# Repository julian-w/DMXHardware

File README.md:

# DMXHardware
DMX Hardware (and Firmware) which allows you build your own DMX equipment

work in progress...

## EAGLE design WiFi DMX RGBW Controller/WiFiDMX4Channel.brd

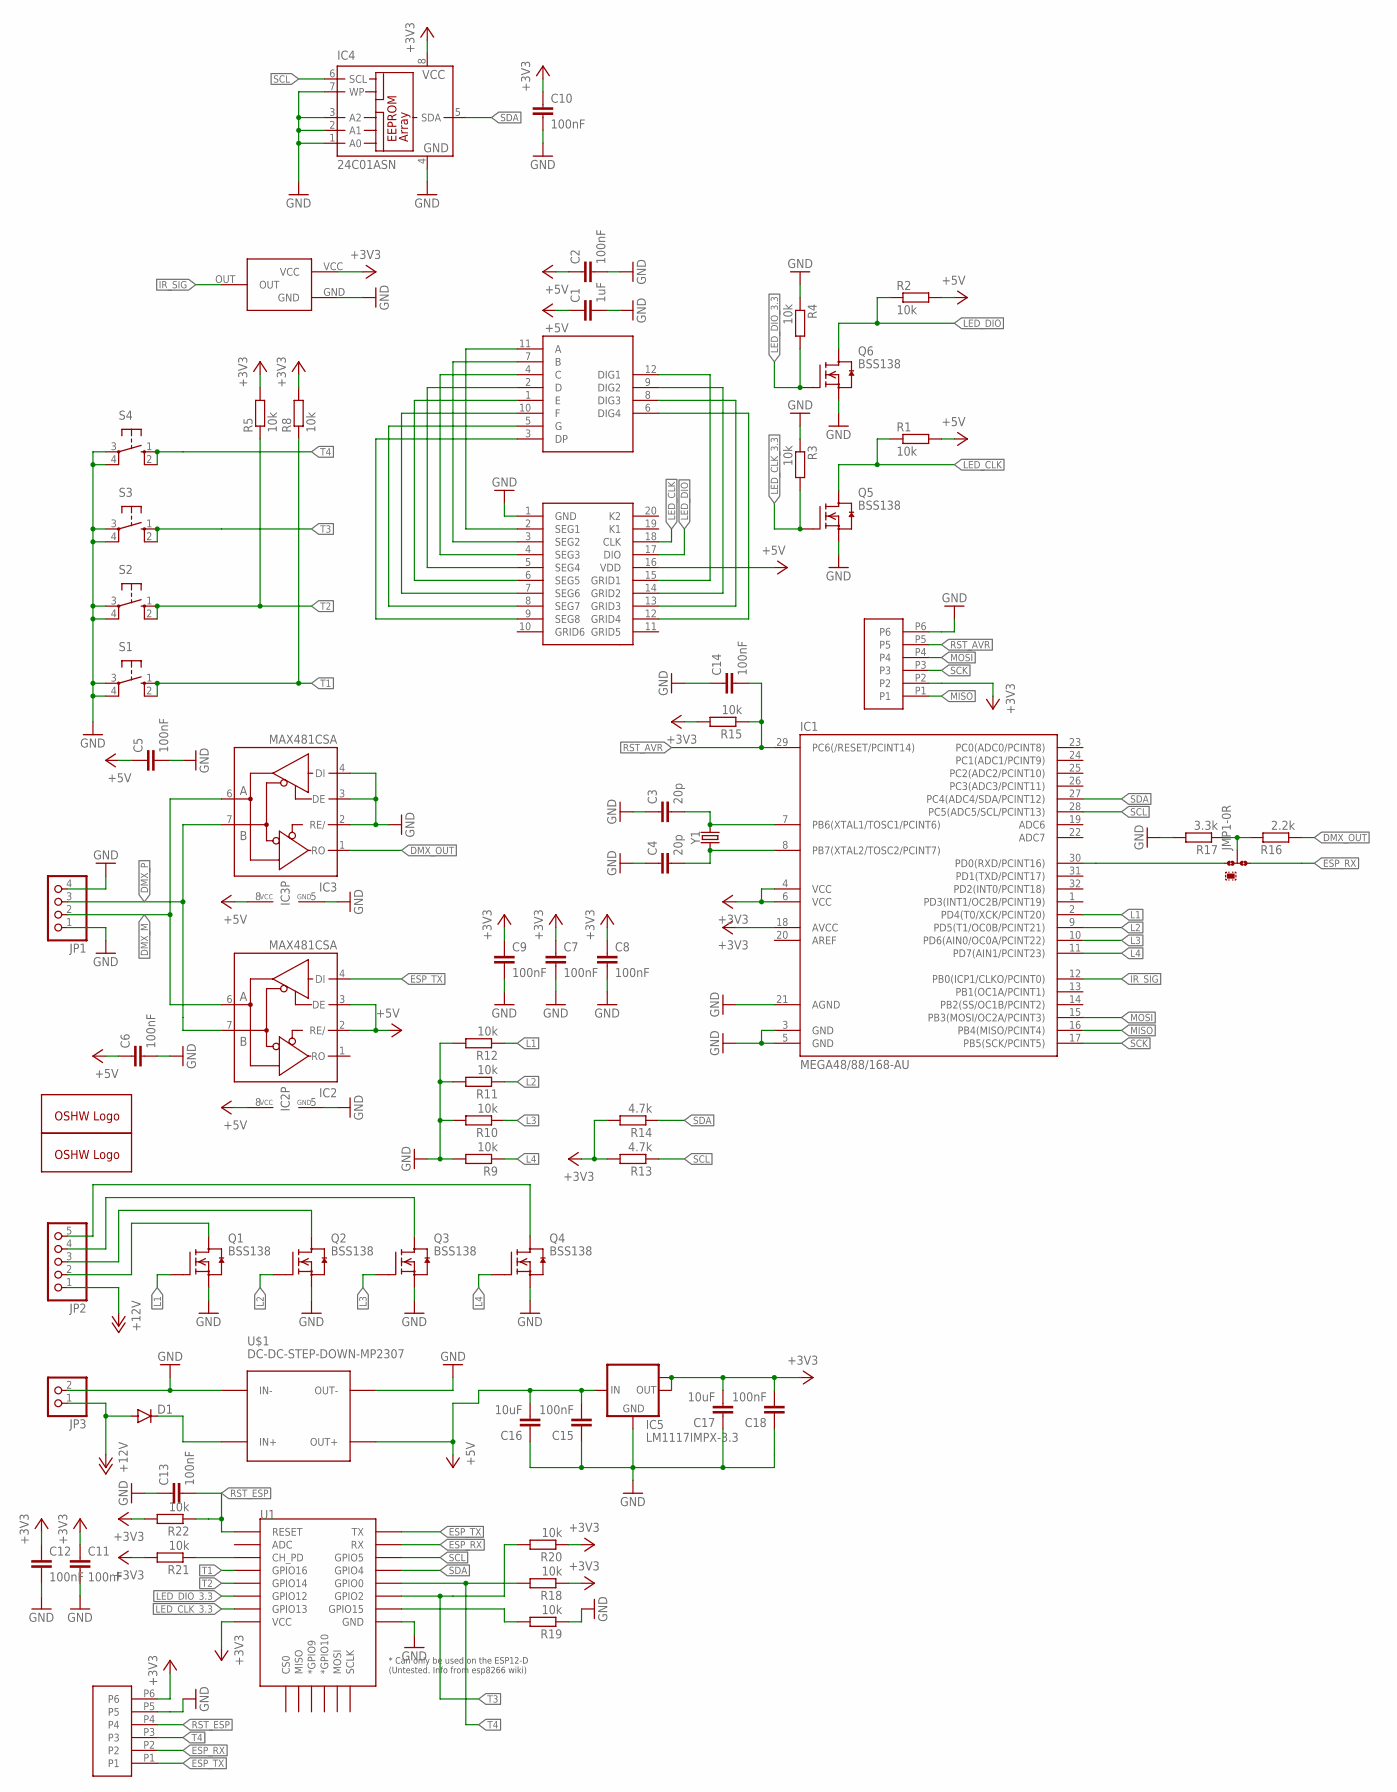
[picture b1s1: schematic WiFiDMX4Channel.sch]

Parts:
C1: 1uF; C0603
C2, C5, C6, C7, C8, C9, C10, C11, C12, C13, C14, C15, C18: 100nF; C0603
C3, C4: 20p; C0603
C16, C17: 10uF; C0603
D1: DIODE-DO214AC; DO214AC
GOLD_ORB_SM1, GOLD_ORB_SM2: OSHWLOGOLOGO5MM; OSHW_5MM
IC1: MEGA48/88/168-AU; TQFP32-08
IC2, IC3: MAX481CSA; SO08
IC4: 24C01ASN; SO-08
IC5: LM1117IMPX-3.3; SOT223
JMP1: 0R-JUMPA; A0R-JMP
JP1: PINHD-1X4_2.54; 1X04
JP2: PINHD-1X5_2.54; 1X05
JP3: PINHD-1X2_2.54; 1X02
Q1, Q2, Q3, Q4, Q5, Q6: BSS138; SOT23
R1, R2, R3, R4, R5, R8, R9, R10, R11, R12, R15, R18, R19, R20, R21, R22: 10k; R0603
R13, R14: 4.7k; R0603
R16: 2.2k; R0603
R17: 3.3k; R0603
S1, S2, S3, S4: 10-XX; B3F-10XX
U1: ESP12ESMD; ESP12E-SMD
U$1: DC-DC-STEP-DOWN-MP2307
U$2: 4-DIGIT-7-SEGMENT; 7SETG-1
U$3: TM1637-SOP20; SO20W
U$4: PC838
U$5, U$6: 6P-1.27
Y1: CRYSTALSMD-5X3.2-2PAD; CRYSTAL-SMD-5X3.2-2PAD

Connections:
+3V3: C7.1, C8.1, C9.1, C10.1, C11.1, C12.1, C17.2, C18.2, IC1.4 (VCC), IC1.6 (VCC), IC1.18 (AVCC), IC4.8 (VCC), IC5.2 (OUT), IC5.TAB (OUT1), R5.2, R8.2, R13.2, R14.2, R15.2, R18.1, R20.1, R21.2, R22.2, U1.VCC, U$4.VCC, U$5.P6, U$6.P2
+5V: C1.1, C2.1, C5.1, C6.1, C15.2, C16.2, IC2.2 (RE/), IC2.3 (DE), IC2.8 (VCC), IC3.8 (VCC), IC5.3 (IN), R1.2, R2.2, U$1.OUT+, U$3.16 (VDD)
+12V: D1.A, JP2.1, JP3.1
AS: R19.2, U1.GPIO15
DMX_M: IC2.6 (A), IC3.6 (A), JP1.2
DMX_OUT: IC3.1 (RO), R16.1
DMX_P: IC2.7 (B), IC3.7 (B), JP1.3
ESP_RX: JMP1.3, U1.RXD0 (RX), U$5.P2
ESP_TX: IC2.4 (DI), U1.TXD0 (TX), U$5.P1
GND: C1.2, C2.2, C3.1, C4.1, C5.2, C6.2, C7.2, C8.2, C9.2, C10.2, C11.2, C12.2, C13.1, C14.1, C15.1, C16.1, C17.1, C18.1, IC1.3 (GND), IC1.5 (GND), IC1.21 (AGND), IC2.5 (GND), IC3.2 (RE/), IC3.3 (DE), IC3.4 (DI), IC3.5 (GND), IC4.1 (A0), IC4.2 (A1), IC4.3 (A2), IC4.4 (GND), IC4.7 (WP), IC5.1 (GND), JP1.1, JP1.4, JP3.2, Q1.2 (S), Q2.2 (S), Q3.2 (S), Q4.2 (S), Q5.2 (S), Q6.2 (S), R3.1, R4.1, R9.2, R10.2, R11.2, R12.2, R17.2, R19.1, S1.3, S1.4 (P1), S2.3, S2.4 (P1), S3.3, S3.4 (P1), S4.3, S4.4 (P1), U1.GND, U$1.IN-, U$1.OUT-, U$3.1 (GND), U$4.GND, U$5.P5, U$6.P6
IR_SIG: IC1.12 (PB0(ICP1/CLKO/PCINT0)), U$4.OUT
L1: IC1.2 (PD4(T0/XCK/PCINT20)), Q1.1 (G), R12.1
L2: IC1.9 (PD5(T1/OC0B/PCINT21)), Q2.1 (G), R11.1
L3: IC1.10 (PD6(AIN0/OC0A/PCINT22)), Q3.1 (G), R10.1
L4: IC1.11 (PD7(AIN1/PCINT23)), Q4.1 (G), R9.1
LED_CLK: Q5.3 (D), R1.1, U$3.18 (CLK)
LED_CLK_3.3: Q5.1 (G), R3.2, U1.GPIO13
LED_DIO: Q6.3 (D), R2.1, U$3.17 (DIO)
LED_DIO_3.3: Q6.1 (G), R4.2, U1.GPIO12
MISO: IC1.16 (PB4(MISO/PCINT4)), U$6.P1
MOSI: IC1.15 (PB3(MOSI/OC2A/PCINT3)), U$6.P4
unnamed: JP2.5, Q4.3 (D)
unnamed: JP2.4, Q3.3 (D)
unnamed: JP2.3, Q2.3 (D)
unnamed: D1.C, U$1.IN+
unnamed: C4.2, IC1.8 (PB7(XTAL2/TOSC2/PCINT7)), Y1.P$1 (1)
unnamed: U$2.11 (A), U$3.2 (SEG1)
unnamed: U$2.7 (B), U$3.3 (SEG2)
unnamed: U$2.4 (C), U$3.4 (SEG3)
unnamed: U$2.2 (D), U$3.5 (SEG4)
unnamed: U$2.1 (E), U$3.6 (SEG5)
unnamed: U$2.10 (F), U$3.7 (SEG6)
unnamed: U$2.5 (G), U$3.8 (SEG7)
unnamed: U$2.3 (DP), U$3.9 (SEG8)
unnamed: U$2.12 (DIG1), U$3.15 (GRID1)
unnamed: U$2.9 (DIG2), U$3.14 (GRID2)
unnamed: U$2.8 (DIG3), U$3.13 (GRID3)
unnamed: U$2.6 (DIG4), U$3.12 (GRID4)
unnamed: C3.2, IC1.7 (PB6(XTAL1/TOSC1/PCINT6)), Y1.P$2 (2)
unnamed: JP2.2, Q1.3 (D)
unnamed: JMP1.2, R16.2, R17.1
unnamed: R21.1, U1.CH_PD
unnamed: IC1.30 (PD0(RXD/PCINT16)), JMP1.1
RST_AVR: C14.2, IC1.29 (PC6(/RESET/PCINT14)), R15.1, U$6.P5
RST_ESP: C13.2, R22.1, U1.RESET, U$5.P4
SCK: IC1.17 (PB5(SCK/PCINT5)), U$6.P3
SCL: IC1.28 (PC5(ADC5/SCL/PCINT13)), IC4.6 (SCL), R13.1, U1.GPIO5
SDA: IC1.27 (PC4(ADC4/SDA/PCINT12)), IC4.5 (SDA), R14.1, U1.GPIO4
T1: R8.1, S1.1 (S), S1.2 (S1), U1.GPIO16
T2: R5.1, S2.1 (S), S2.2 (S1), U1.GPIO14
T3: R20.2, S3.1 (S), S3.2 (S1), U1.GPIO2
T4: R18.2, S4.1 (S), S4.2 (S1), U1.GPIO0, U$5.P3

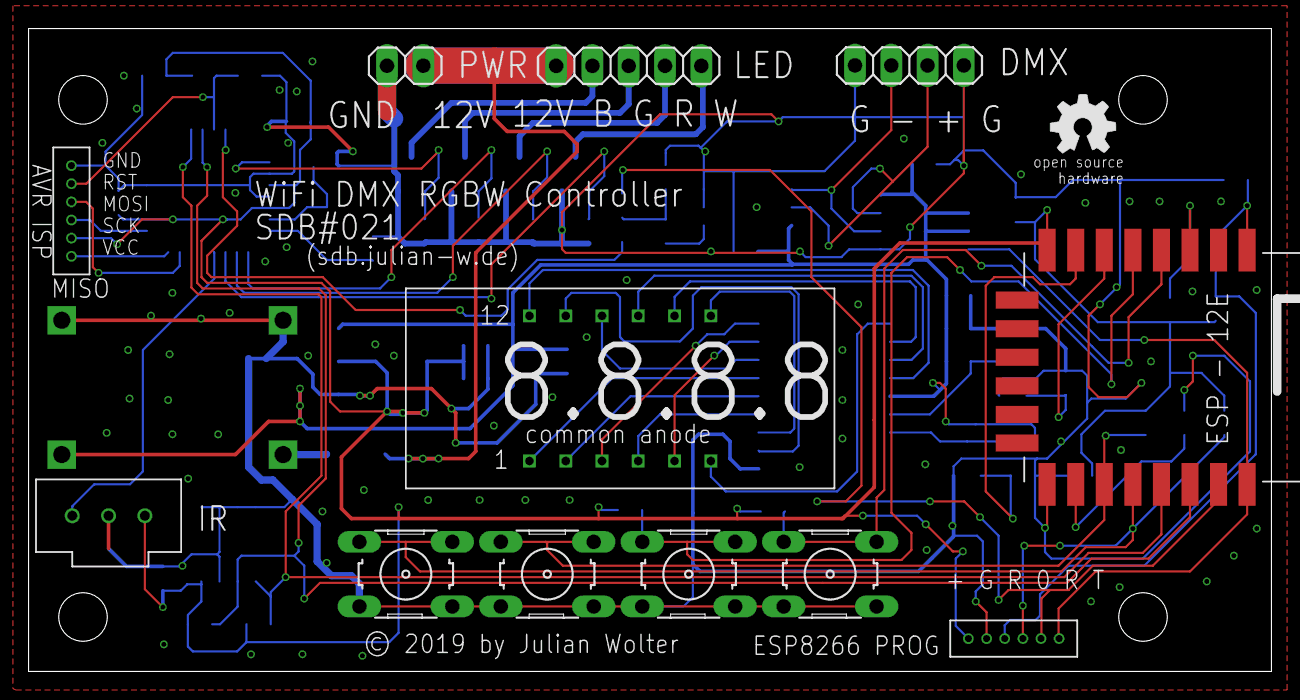
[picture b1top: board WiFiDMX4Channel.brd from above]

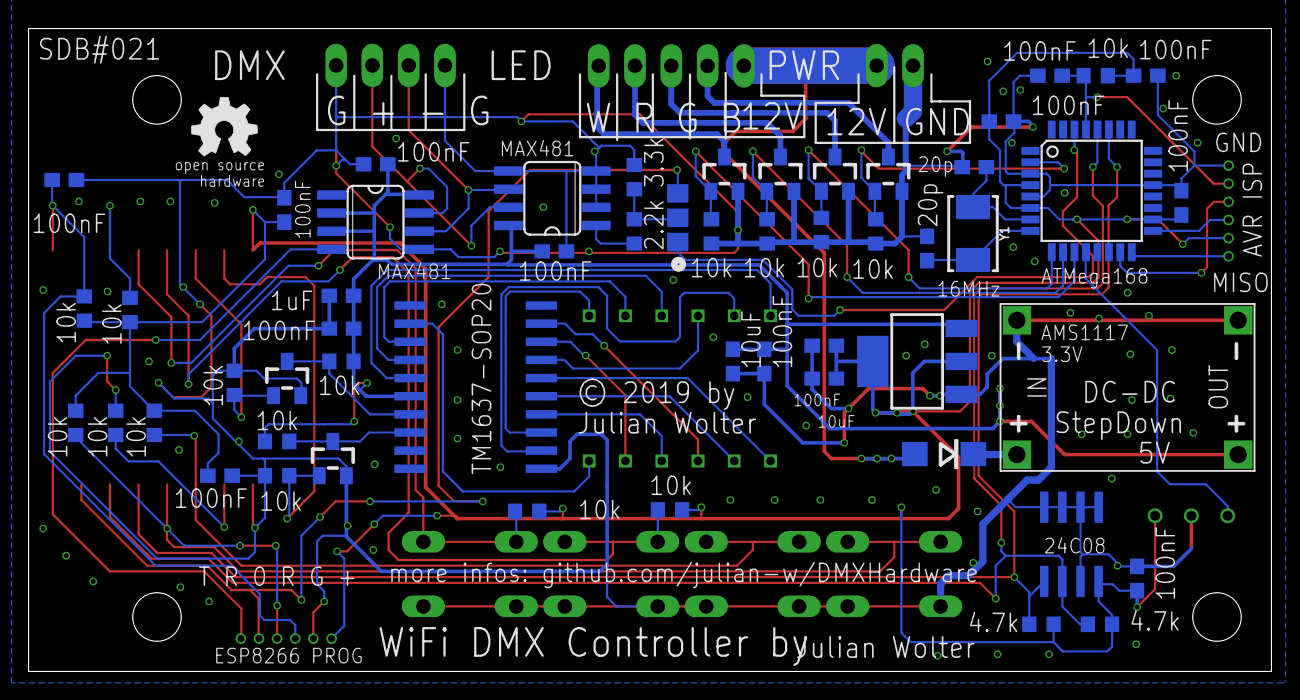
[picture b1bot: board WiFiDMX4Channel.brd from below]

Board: 2 copper layers, 87.0 x 45.0 mm, 68 parts (55 on the bottom side), 52 nets.

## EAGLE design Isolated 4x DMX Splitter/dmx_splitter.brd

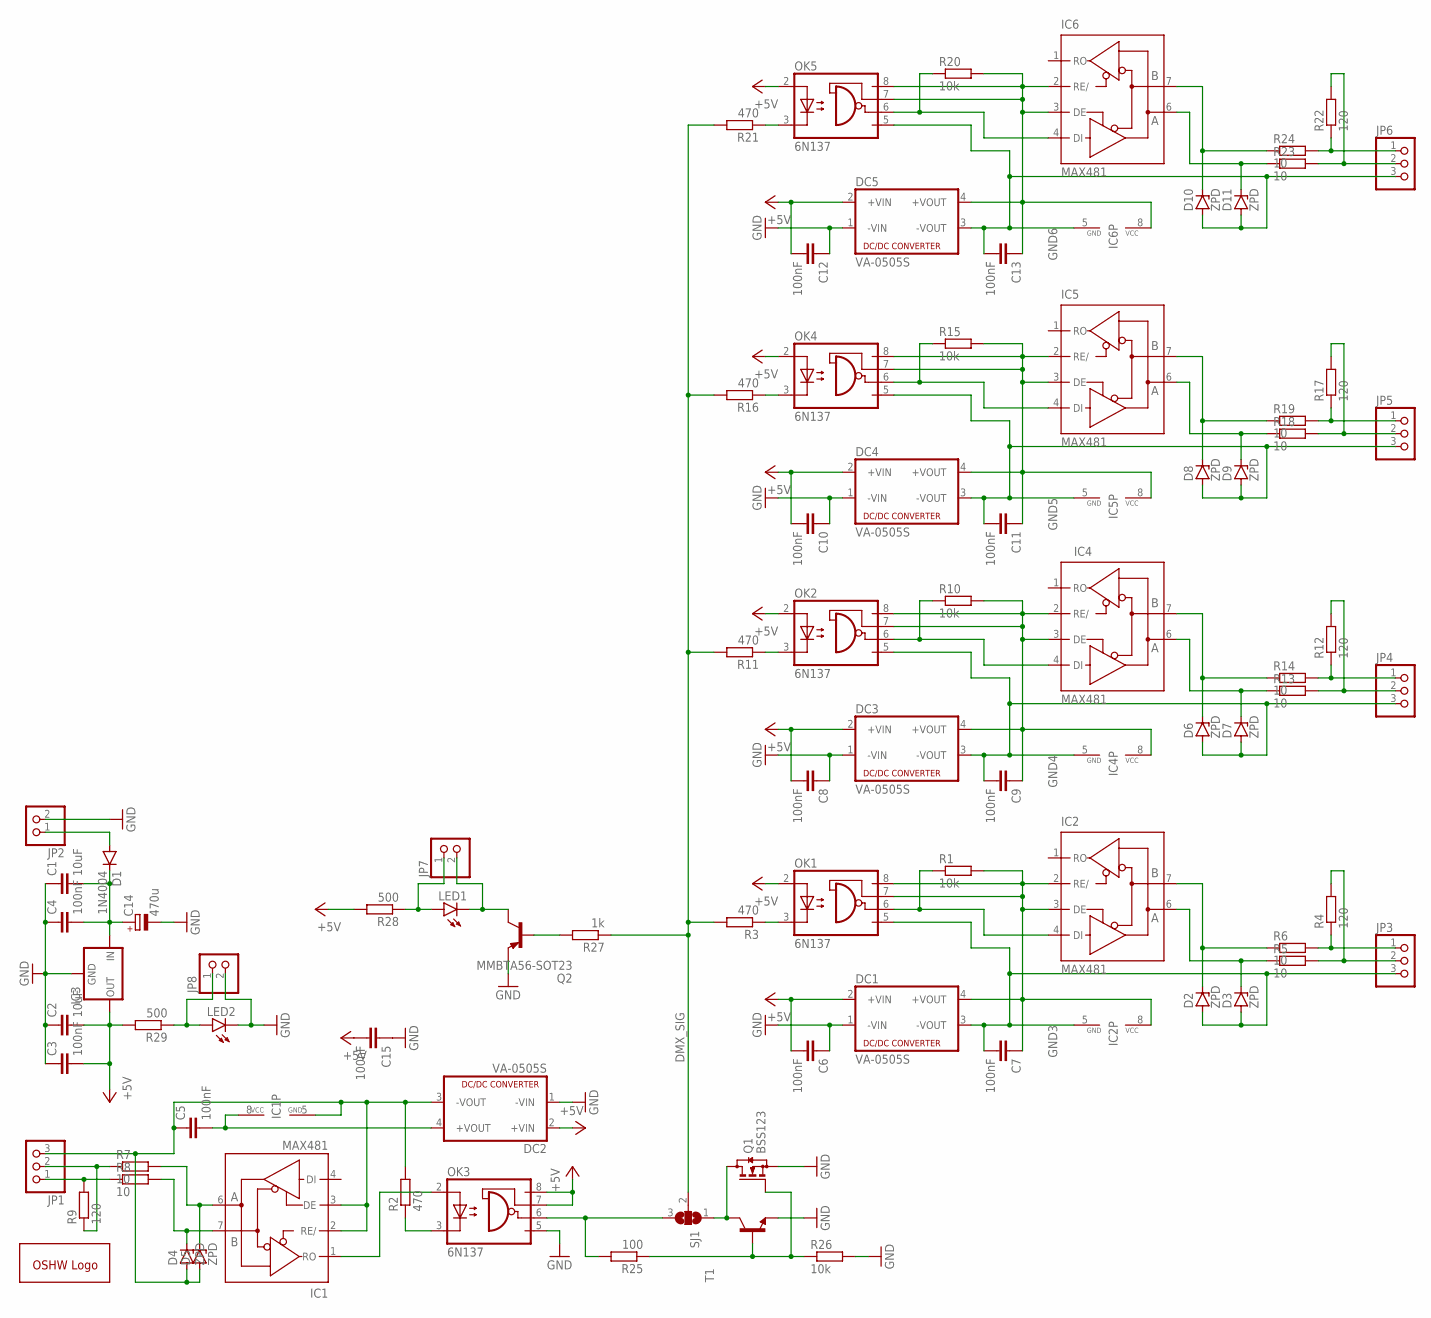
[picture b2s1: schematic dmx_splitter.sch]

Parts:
C1, C2: 10uF; C1206
C3, C4, C5, C6, C7, C8, C9, C10, C11, C12, C13, C15: 100nF; C1206
C14: 470u; E2,5-7
D1: 1N4004; DO41-10
D2, D3, D4, D5, D6, D7, D8, D9, D10, D11: ZPD; DO35Z10
DC1, DC2, DC3, DC4, DC5: VA-0505S; 4SIL
GOLD_ORB_SM1: OSHWLOGOLOGO5MM; OSHW_5MM
IC1, IC2, IC4, IC5, IC6: MAX481; DIL08
IC3: 78XXS
JP1, JP3, JP4, JP5, JP6: PINHD-1X3; 1X03
JP2, JP7, JP8: PINHD-1X2; 1X02
LED1, LED2: LEDCHIPLED_1206; CHIPLED_1206
OK1, OK2, OK3, OK4, OK5: 6N137; DIL08
Q1: BSS123; SOT23
Q2: MMBTA56-SOT23; SOT23
R1, R10, R15, R20, R26: 10k; R1206
R2, R3, R11, R16, R21: 470; R1206
R4, R9, R12, R17, R22: 120; R1206
R5, R6, R7, R8, R13, R14, R18, R19, R23, R24: 10; R1206
R25: 100; R1206
R27: 1k; R1206
R28, R29: 500; R1206
SJ1: SJ2W; SJ_2
T1: -NPN-SOT23-EBC; SOT23-EBC

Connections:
+5V: C2.2, C3.2, C6.2, C8.2, C10.2, C12.2, C15.2, DC1.2 (+VIN), DC2.2 (+VIN), DC3.2 (+VIN), DC4.2 (+VIN), DC5.2 (+VIN), IC3.OUT, OK1.2 (A), OK2.2 (A), OK3.7 (VE), OK3.8 (VCC), OK4.2 (A), OK5.2 (A), R28.2, R29.2
DMX_SIG: R3.2, R11.2, R16.2, R21.2, R27.1, SJ1.2
GND: C1.1, C2.1, C3.1, C4.1, C6.1, C8.1, C10.1, C12.1, C14.-, C15.1, DC1.1 (-VIN), DC2.1 (-VIN), DC3.1 (-VIN), DC4.1 (-VIN), DC5.1 (-VIN), IC3.GND, JP2.2, JP8.2, LED2.C, OK3.5 (GND), Q1.2 (S), Q2.2 (E), R26.2, T1.E
GND2: C5.1, D4.A, D5.A, DC2.3 (-VOUT), IC1.2 (RE/), IC1.3 (DE), IC1.5 (GND), JP1.3, R2.2
GND3: C7.2, D2.A, D3.A, DC1.3 (-VOUT), IC2.5 (GND), JP3.3, OK1.5 (GND)
GND4: C9.2, D6.A, D7.A, DC3.3 (-VOUT), IC4.5 (GND), JP4.3, OK2.5 (GND)
GND5: C11.2, D8.A, D9.A, DC4.3 (-VOUT), IC5.5 (GND), JP5.3, OK4.5 (GND)
GND6: C13.2, D10.A, D11.A, DC5.3 (-VOUT), IC6.5 (GND), JP6.3, OK5.5 (GND)
unnamed: D1.A, JP2.1
unnamed: C1.2, C4.2, C14.+, D1.C, IC3.IN
unnamed: OK1.3 (C), R3.1
unnamed: C5.2, DC2.4 (+VOUT), IC1.8 (VCC)
unnamed: JP1.1, R8.1, R9.2
unnamed: JP1.2, R7.1, R9.1
unnamed: IC1.1 (RO), OK3.2 (A)
unnamed: OK3.3 (C), R2.1
unnamed: C7.1, DC1.4 (+VOUT), IC2.2 (RE/), IC2.3 (DE), IC2.8 (VCC), OK1.7 (VE), OK1.8 (VCC), R1.2
unnamed: JP3.2, R4.2, R5.2
unnamed: JP3.1, R4.1, R6.2
unnamed: IC2.4 (DI), OK1.6 (VO), R1.1
unnamed: D3.C, IC2.6 (A), R5.1
unnamed: D2.C, IC2.7 (B), R6.1
unnamed: Q1.3 (D), SJ1.1, T1.C
unnamed: D4.C, IC1.7 (B), R8.2
unnamed: D5.C, IC1.6 (A), R7.2
unnamed: Q2.1 (B), R27.2
unnamed: Q1.1 (G), R25.1, R26.1, T1.B
unnamed: OK3.6 (VO), R25.2, SJ1.3
unnamed: OK2.3 (C), R11.1
unnamed: JP7.1, LED1.A, R28.1
unnamed: C9.1, DC3.4 (+VOUT), IC4.2 (RE/), IC4.3 (DE), IC4.8 (VCC), OK2.7 (VE), OK2.8 (VCC), R10.2
unnamed: IC4.4 (DI), OK2.6 (VO), R10.1
unnamed: D7.C, IC4.6 (A), R13.1
unnamed: D6.C, IC4.7 (B), R14.1
unnamed: JP4.2, R12.2, R13.2
unnamed: JP4.1, R12.1, R14.2
unnamed: OK4.3 (C), R16.1
unnamed: JP7.2, LED1.C, Q2.3 (C)
unnamed: C11.1, DC4.4 (+VOUT), IC5.2 (RE/), IC5.3 (DE), IC5.8 (VCC), OK4.7 (VE), OK4.8 (VCC), R15.2
unnamed: IC5.4 (DI), OK4.6 (VO), R15.1
unnamed: D9.C, IC5.6 (A), R18.1
unnamed: D8.C, IC5.7 (B), R19.1
unnamed: JP5.2, R17.2, R18.2
unnamed: JP5.1, R17.1, R19.2
unnamed: OK5.3 (C), R21.1
unnamed: C13.1, DC5.4 (+VOUT), IC6.2 (RE/), IC6.3 (DE), IC6.8 (VCC), OK5.7 (VE), OK5.8 (VCC), R20.2
unnamed: IC6.4 (DI), OK5.6 (VO), R20.1
unnamed: D11.C, IC6.6 (A), R23.1
unnamed: D10.C, IC6.7 (B), R24.1
unnamed: JP6.2, R22.2, R23.2
unnamed: JP6.1, R22.1, R24.2
unnamed: JP8.1, LED2.A, R29.1

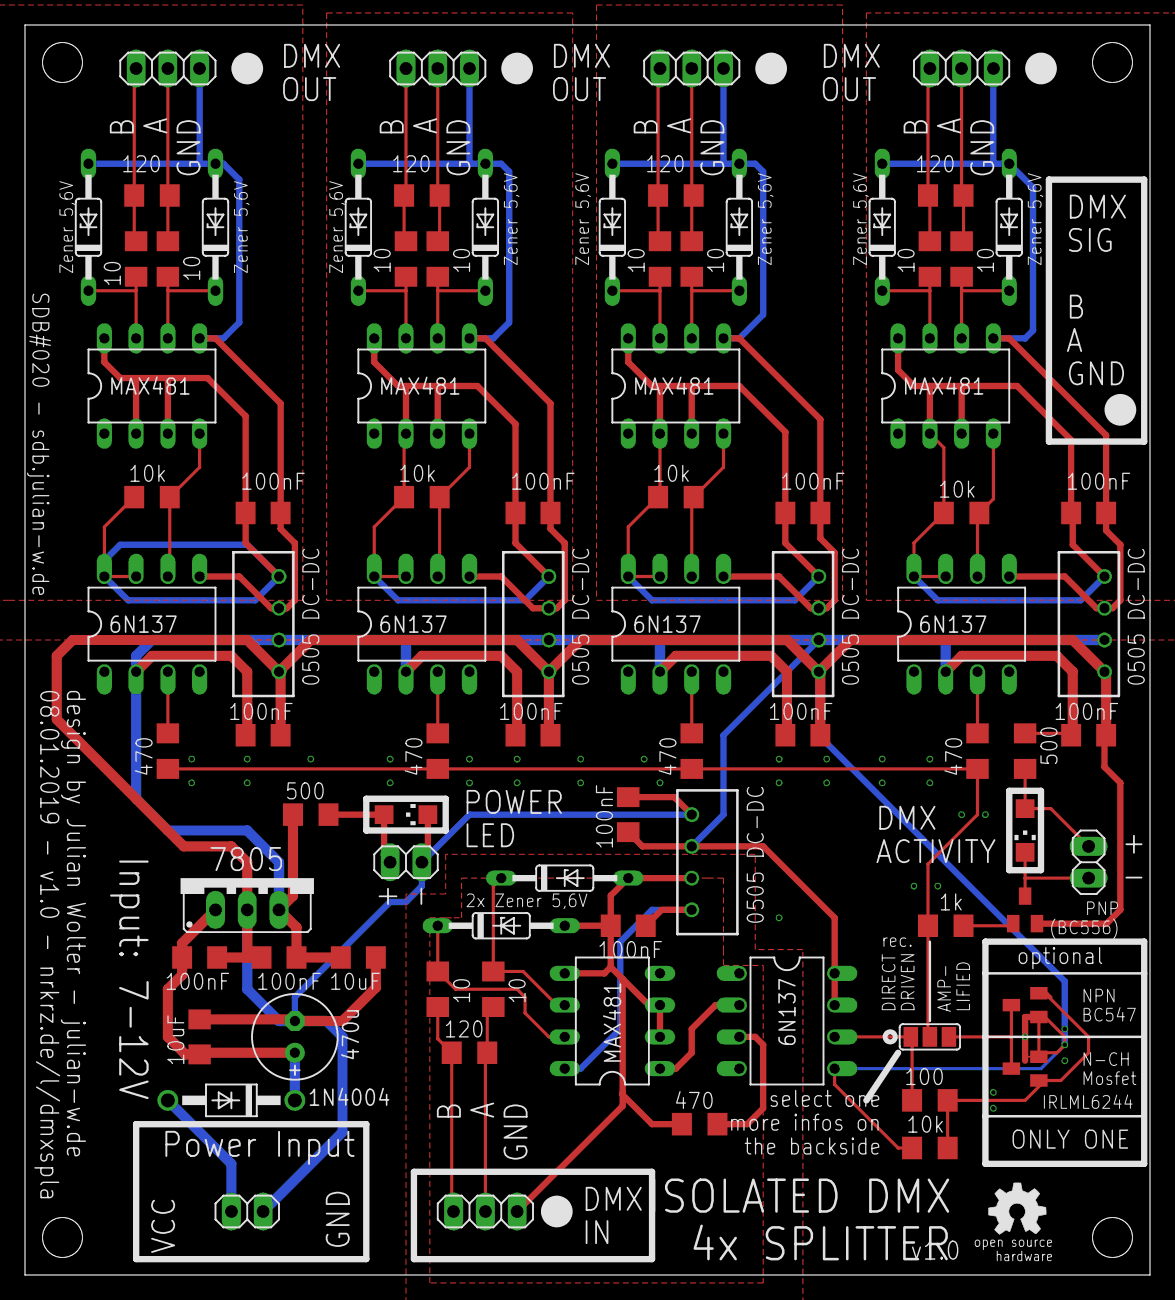
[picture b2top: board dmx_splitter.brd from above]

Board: 2 copper layers, 90.0 x 100.0 mm, 86 parts (0 on the bottom side), 52 nets.

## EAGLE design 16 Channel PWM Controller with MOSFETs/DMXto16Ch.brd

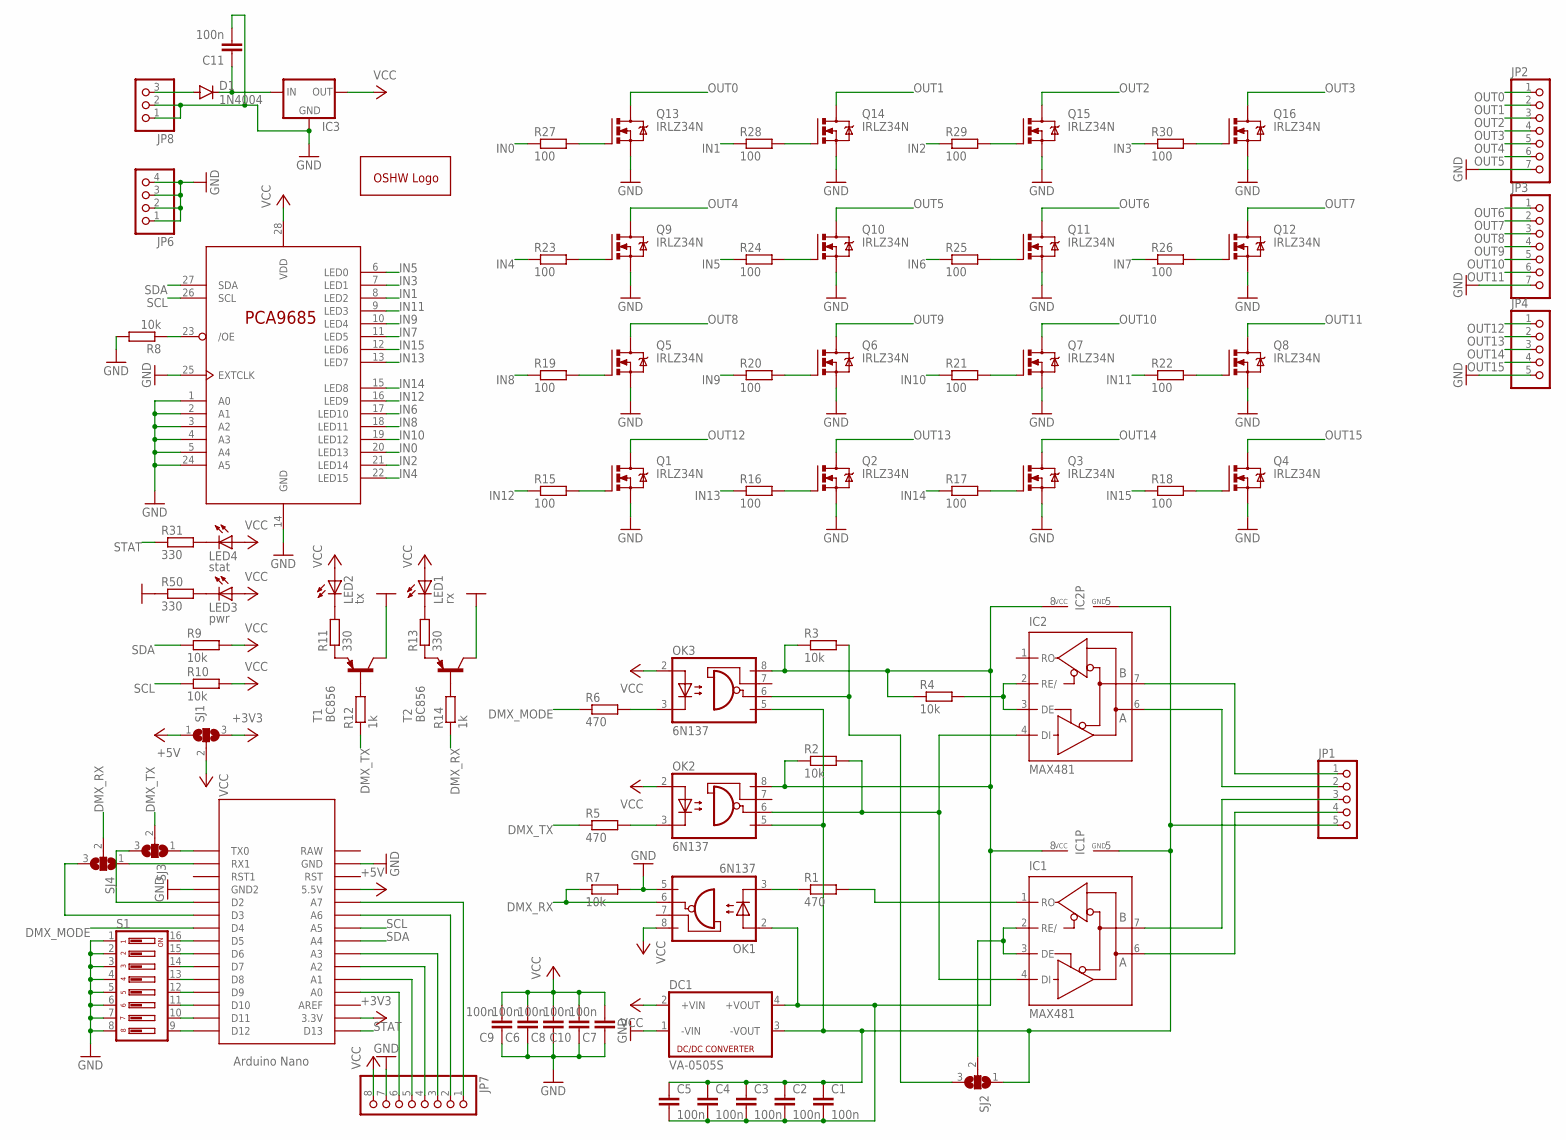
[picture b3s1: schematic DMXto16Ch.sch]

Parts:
C1, C2, C3, C4, C5, C6, C7, C8, C9, C10, C11: 100n; C1206
D1: 1N4004; DO41-10
DC1: VA-0505S; 4SIL
GOLD_ORB_SM1: OSHWLOGOLOGO5MM; OSHW_5MM
IC1, IC2: MAX481; DIL08
IC3: 78XXS
JP1, JP4: PINHD-1X5; 1X05
JP2, JP3: PINHD-1X7; 1X07
JP6: PINHD-1X4; 1X04
JP7: PINHD-1X8; 1X08
JP8: PINHD-1X3; 1X03
LED1: rx; 1206
LED2: tx; 1206
LED3: pwr; 1206
LED4: stat; 1206
OK1, OK2, OK3: 6N137; DIL08
Q1, Q2, Q3, Q4, Q5, Q6, Q7, Q8, Q9, Q10, Q11, Q12, Q13, Q14, Q15, Q16: IRLZ34N; TO220BV
R1, R5, R6: 470; R1206
R2, R3, R4, R7, R8, R9, R10: 10k; R1206
R11, R13, R31, R50: 330; R1206
R12, R14: 1k; R1206
R15, R16, R17, R18, R19, R20, R21, R22, R23, R24, R25, R26, R27, R28, R29, R30: 100; R1206
S1: DIP08YL
SJ1, SJ2, SJ3, SJ4: SJ2W; SJ_2
T1, T2: BC856; SOT23-BCE
U$1: NANO
U$2: PCA9685PW; TSSOP28

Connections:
+3V3: SJ1.3, U$1.3.3V
+5V: SJ1.1, U$1.5V (5.5V)
DMX_MODE: R6.1, U$1.D4
DMX_RX: OK1.6 (VO), R7.1, R14.1, SJ4.2
DMX_TX: R5.1, R12.1, SJ3.2
GND: C6.1, C7.1, C8.1, C9.1, C10.1, C11.2, DC1.1 (-VIN), IC3.GND, JP2.7, JP3.7, JP4.5, JP6.1, JP6.2, JP6.3, JP6.4, JP7.7, JP8.1, JP8.2, OK1.5 (GND), Q1.S, Q2.S, Q3.S, Q4.S, Q5.S, Q6.S, Q7.S, Q8.S, Q9.S, Q10.S, Q11.S, Q12.S, Q13.S, Q14.S, Q15.S, Q16.S, R7.2, R8.2, R50.1, S1.1, S1.2, S1.3, S1.4, S1.5, S1.6, S1.7, S1.8, T1.C, T2.C, U$1.GND, U$1.GND1 (GND2), U$2.1 (A0), U$2.2 (A1), U$2.3 (A2), U$2.4 (A3), U$2.5 (A4), U$2.14 (GND), U$2.24 (A5), U$2.25 (EXTCLK)
IN0: R27.1, U$2.20 (LED13)
IN1: R28.1, U$2.8 (LED2)
IN2: R29.1, U$2.21 (LED14)
IN3: R30.1, U$2.7 (LED1)
IN4: R23.1, U$2.22 (LED15)
IN5: R24.1, U$2.6 (LED0)
IN6: R25.1, U$2.17 (LED10)
IN7: R26.1, U$2.11 (LED5)
IN8: R19.1, U$2.18 (LED11)
IN9: R20.1, U$2.10 (LED4)
IN10: R21.1, U$2.19 (LED12)
IN11: R22.1, U$2.9 (LED3)
IN12: R15.1, U$2.16 (LED9)
IN13: R16.1, U$2.13 (LED7)
IN14: R17.1, U$2.15 (LED8)
IN15: R18.1, U$2.12 (LED6)
unnamed: C1.2, C2.2, C3.2, C4.2, C5.2, DC1.4 (+VOUT), IC1.8 (VCC), IC2.8 (VCC), OK1.2 (A), OK2.8 (VCC), OK3.8 (VCC), R2.1, R3.1, R4.1
unnamed: R8.1, U$2.23 (/OE)
unnamed: IC2.7 (B), JP1.1
unnamed: IC2.6 (A), JP1.2
unnamed: IC1.7 (B), JP1.3
unnamed: IC1.6 (A), JP1.4
unnamed: R12.2, T1.B
unnamed: OK1.3 (C), R1.1
unnamed: IC1.1 (RO), R1.2
unnamed: IC1.4 (DI), IC2.4 (DI), OK2.6 (VO), R2.2
unnamed: C1.1, C2.1, C3.1, C4.1, C5.1, DC1.3 (-VOUT), IC1.5 (GND), IC2.5 (GND), JP1.5, OK2.5 (GND), OK3.5 (GND), SJ2.1
unnamed: OK3.6 (VO), R3.2, SJ2.3
unnamed: R13.1, T2.E
unnamed: IC1.2 (RE/), IC1.3 (DE), SJ2.2
unnamed: IC2.2 (RE/), IC2.3 (DE), R4.2
unnamed: LED1.C, R13.2
unnamed: R14.2, T2.B
unnamed: OK2.3 (C), R5.2
unnamed: OK3.3 (C), R6.2
unnamed: Q1.G, R15.2
unnamed: Q2.G, R16.2
unnamed: Q3.G, R17.2
unnamed: Q4.G, R18.2
unnamed: Q5.G, R19.2
unnamed: Q6.G, R20.2
unnamed: R11.1, T1.E
unnamed: LED2.C, R11.2
unnamed: Q7.G, R21.2
unnamed: Q8.G, R22.2
unnamed: Q9.G, R23.2
unnamed: Q10.G, R24.2
unnamed: Q11.G, R25.2
unnamed: Q12.G, R26.2
unnamed: Q13.G, R27.2
unnamed: Q14.G, R28.2
unnamed: Q15.G, R29.2
unnamed: Q16.G, R30.2
unnamed: S1.9, U$1.D12
unnamed: S1.10, U$1.D11
unnamed: S1.11, U$1.D10
unnamed: S1.12, U$1.D9
unnamed: S1.13, U$1.D8
unnamed: S1.14, U$1.D7
unnamed: S1.15, U$1.D6
unnamed: S1.16, U$1.D5
unnamed: SJ4.1, U$1.RX1
unnamed: SJ3.1, U$1.TX0
unnamed: SJ3.3, U$1.D2
unnamed: SJ4.3, U$1.D3
unnamed: LED3.C, R50.2
unnamed: D1.A, JP8.3
unnamed: C11.1, D1.C, IC3.IN
unnamed: JP7.1, U$1.A7
unnamed: JP7.2, U$1.A6
unnamed: JP7.3, U$1.A3
unnamed: JP7.4, U$1.A2
unnamed: JP7.5, U$1.A1
unnamed: JP7.6, U$1.A0
unnamed: LED4.C, R31.2
OUT0: JP2.1, Q13.D
OUT1: JP2.2, Q14.D
OUT2: JP2.3, Q15.D
OUT3: JP2.4, Q16.D
OUT4: JP2.5, Q9.D
OUT5: JP2.6, Q10.D
OUT6: JP3.1, Q11.D
OUT7: JP3.2, Q12.D
OUT8: JP3.3, Q5.D
OUT9: JP3.4, Q6.D
OUT10: JP3.5, Q7.D
OUT11: JP3.6, Q8.D
OUT12: JP4.1, Q1.D
OUT13: JP4.2, Q2.D
OUT14: JP4.3, Q3.D
OUT15: JP4.4, Q4.D
SCL: R10.1, U$1.A5, U$2.26 (SCL)
SDA: R9.1, U$1.A4, U$2.27 (SDA)
STAT: R31.1, U$1.D13
VCC: C6.2, C7.2, C8.2, C9.2, C10.2, DC1.2 (+VIN), IC3.OUT, JP7.8, LED1.A, LED2.A, LED3.A, LED4.A, OK1.8 (VCC), OK2.2 (A), OK3.2 (A), R9.2, R10.2, SJ1.2, U$2.28 (VDD)

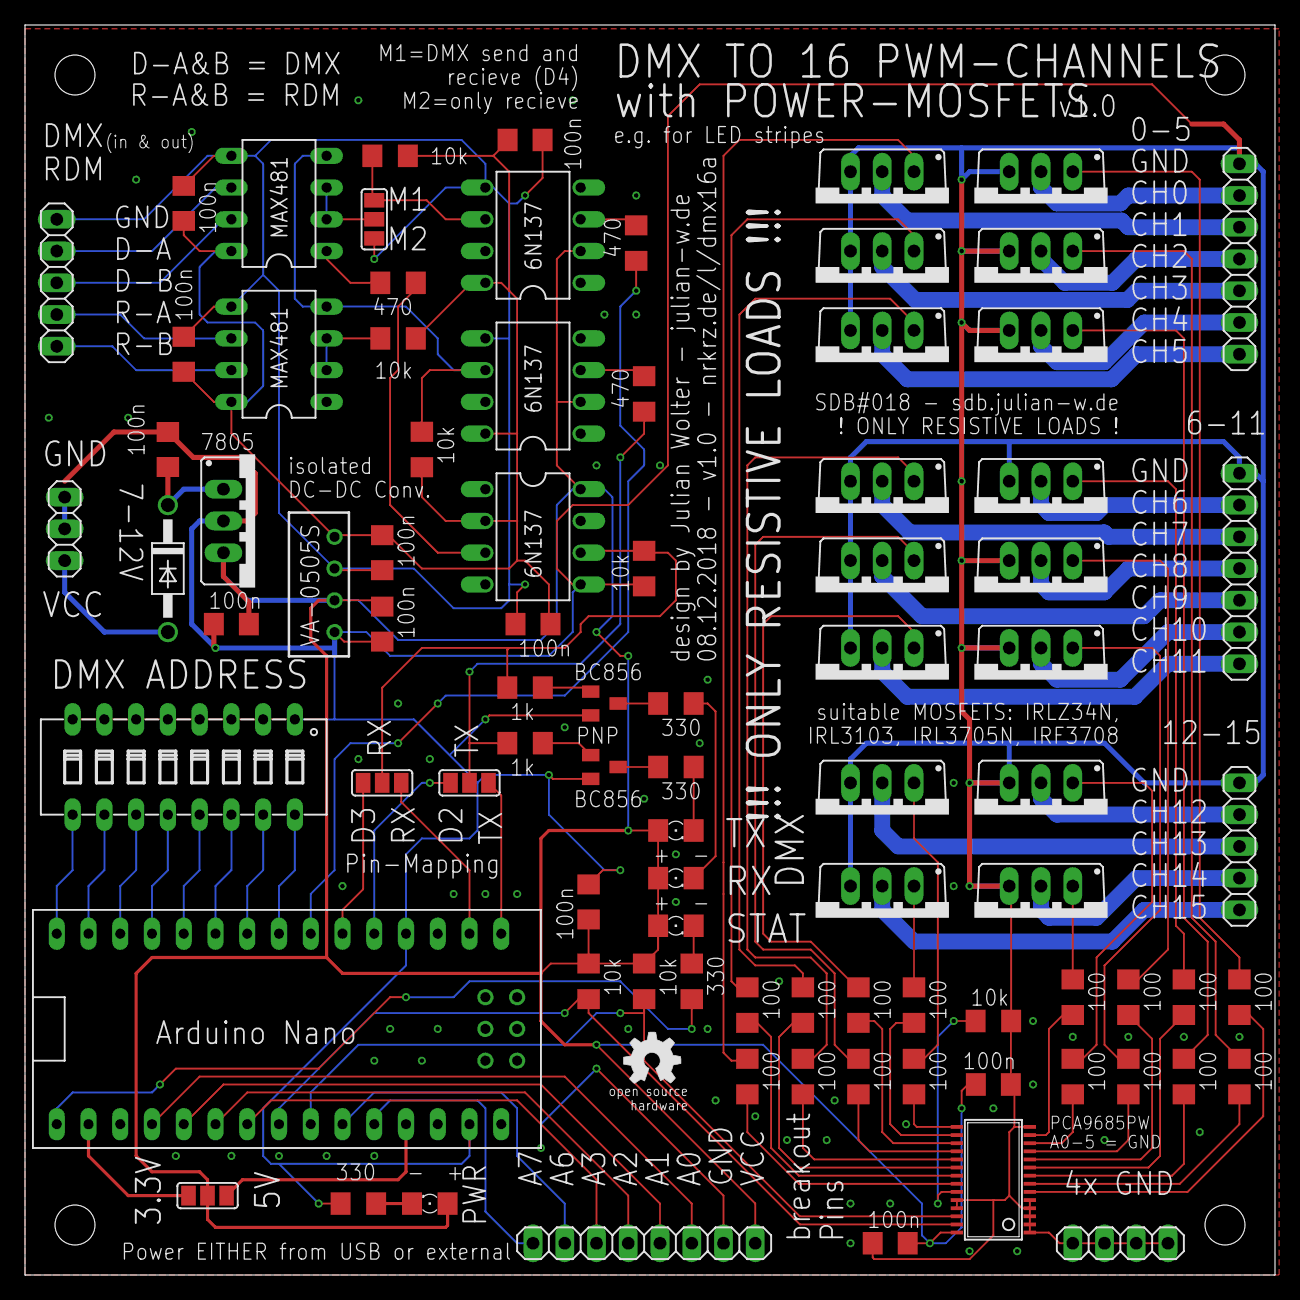
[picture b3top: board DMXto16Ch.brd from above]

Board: 2 copper layers, 100.0 x 100.0 mm, 88 parts (0 on the bottom side), 101 nets.

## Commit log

2019-01-08 Create README.md
    first commit
2019-01-08 added board for a 16 Channel PWM Controller with MOSFETS
2019-01-08 added board for 4x isolated DMX splitter
2019-01-11 fixing mapping of channels
2019-01-11 fixing usage of DMX library
2019-08-01 added new board: 4 Channel DMX with WiFi
2019-10-17 adding PDF renderings of the schematic and the board layout

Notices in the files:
WiFi DMX RGBW Controller/WiFiDMX4Channel.brd:
© 2019 by Julian Wolter
© 2019 by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
parts and their libraries:
m-pad-2.1: License : GNU General Public License version 2 (see bottom)
diy-modules: Released under the Creative Commons Attribution 4.0 International License: http://creativecommons.org/licenses/by/4.0
